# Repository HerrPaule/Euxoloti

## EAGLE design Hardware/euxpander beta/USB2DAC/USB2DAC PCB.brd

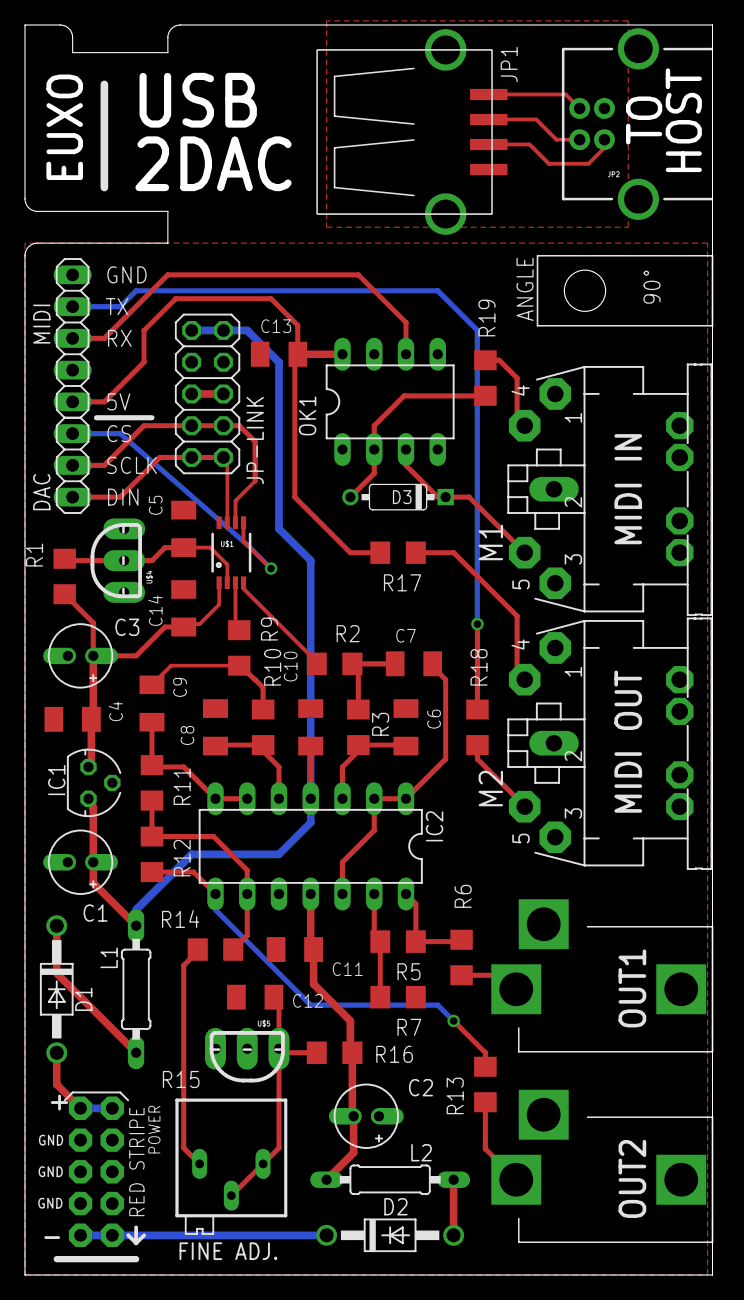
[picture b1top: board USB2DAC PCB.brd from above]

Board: 2 copper layers, 55.0 x 100.0 mm, 53 parts (0 on the bottom side), 41 nets.

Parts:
C1, C2: 47uF; E2-5
C3: 22uF; E2-5
C4, C5, C12: 100nF; C1206K
C6, C7, C8, C9, C10, C11, C13, C14: C1206K
D1, D2: 1N4004; DO41-10
D3: DO35-7
DAC: 1X03
IC1: 78LXX
IC2: TL074P; DIL14
JP1: USB-A-S
JP2: USB-B; USB-B-PTH
JP-LINK: 2X05
L1, L2: 0207/10
M1: MIDI-IN; CP-2350
M2: MIDI-OUT; CP-2350
MIDI: 1X05
OK1: 6N137; DIL08
OUT1, OUT2: PJ302M
R1, R2, R3, R5, R6, R7, R9, R10, R11, R12, R13, R14, R16, R17, R18, R19: R1206
R15: RTRIM3296P
SV1: EURO_POWER_HEADERFAT_PADS; EURO_PWR_HEADER_FAT
U$1: DAC8552; MSOP-8
U$2: WINKEL; WINKEL90°
U$4, U$5: LM4040DIP; TO-92

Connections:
+3V3: C3.+, C4.1, C14.2, IC1.OUT, R1.1, U$1.1
+5V: C13.1, MIDI.5, OK1.8, R17.2
+12V: C1.+, C10.1, IC1.IN, IC2.4, JP-LINK.1, JP-LINK.2, L1.2
-12V: C2.-, C11.2, IC2.11, L2.2, R16.1
GND: C1.-, C2.+, C3.-, C4.2, C5.2, C6.2, C8.2, C10.2, C11.1, C12.2, C13.2, C14.1, IC1.GND, IC2.10, JP-LINK.3, JP-LINK.4, M2.2, M2.PE, M2.PE1, M2.PE2, M2.PE@, MIDI.1, OK1.5, OUT1.GND, OUT2.GND, R7.1, SV1.3, SV1.4, SV1.5, SV1.6, SV1.7, SV1.8, U$1.8, U$4.-, U$5.+
unnamed: DAC.3, U$1.5
unnamed: DAC.2, JP-LINK.7, JP-LINK.8, U$1.6
unnamed: DAC.1, JP-LINK.9, JP-LINK.10, U$1.7
unnamed: D3.A, OK1.2, R19.2
unnamed: M2.5, R18.2
unnamed: D2.C, SV1.1, SV1.2
unnamed: D1.A, SV1.9, SV1.10
unnamed: C6.1, IC2.3, R3.2
unnamed: C7.1, R2.2, R3.1
unnamed: IC2.13, R5.1, R7.2
unnamed: IC2.14, R5.2, R6.1
unnamed: C9.2, IC2.6, IC2.7, R11.1
unnamed: C8.1, IC2.5, R10.2
unnamed: C9.1, R9.2, R10.1
unnamed: IC2.9, R11.2, R12.1, R14.2
unnamed: IC2.8, R12.2, R13.1
unnamed: R14.1, R15.1
unnamed: D2.A, L2.1
unnamed: D1.C, L1.1
unnamed: JP1.VBUS, JP2.VBUS
unnamed: JP1.D-, JP2.D-
unnamed: JP1.D+, JP2.D+
unnamed: M2.4, R17.1
unnamed: M1.4, R19.1
unnamed: JP-LINK.5, JP-LINK.6
unnamed: D3.C, M1.5, OK1.3
unnamed: C7.2, IC2.1, IC2.2, IC2.12
OUT1: OUT1.S, R6.2
OUT2: OUT2.S, R13.2
OUTA: R2.1, U$1.4
OUTB: R9.1, U$1.3
RX: MIDI.3, OK1.6
TX: MIDI.2, R18.1
USB_GND: JP1.GND, JP2.GND
VREF2.5: C5.1, R1.2, U$1.2, U$4.+
VREF-10: C12.1, R15.2, R15.3, R16.2, U$5.-

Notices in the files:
parts and their libraries:
SparkFun-Connectors: Licensing: Creative Commons ShareAlike 4.0 International - https://creativecommons.org/licenses/by-sa/4.0
